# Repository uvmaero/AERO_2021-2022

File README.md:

# AERO_2021-2022

AERO Code and PCBs for CleanSpeed 5.0

This is all the boards and code we generate

## File Structure
Files here are for both the PCB and the firmware. 

{Board_Name}/{Board_Name_Firmware} -> holds the files for the firmware

{Board_Name}/{Board_Name_PCB} -> holds the KiCad files for the PCB

## Board Information

 - BCP: BMS Connector Pass through
 - DCB: Driver Contorl Board
 - HVB: High Voltage Board
 - MRP: Motor Resolver Passthrough
 - RCB: Rear Control Board

To read more about the boards go to [Board Descriptions](Board_Descriptions.md)

## Code Information

Code descrpitions can be found in [Firmware Descriptions](Firmware_Descriptions.md)

## Wireless Transceiver Information

There's also a wireless project. More information to come.

## Willem Review Notes: 

@Willem -> put any notes you have regarding boards here. 
Please review RCB, DCB, HVB, PAM

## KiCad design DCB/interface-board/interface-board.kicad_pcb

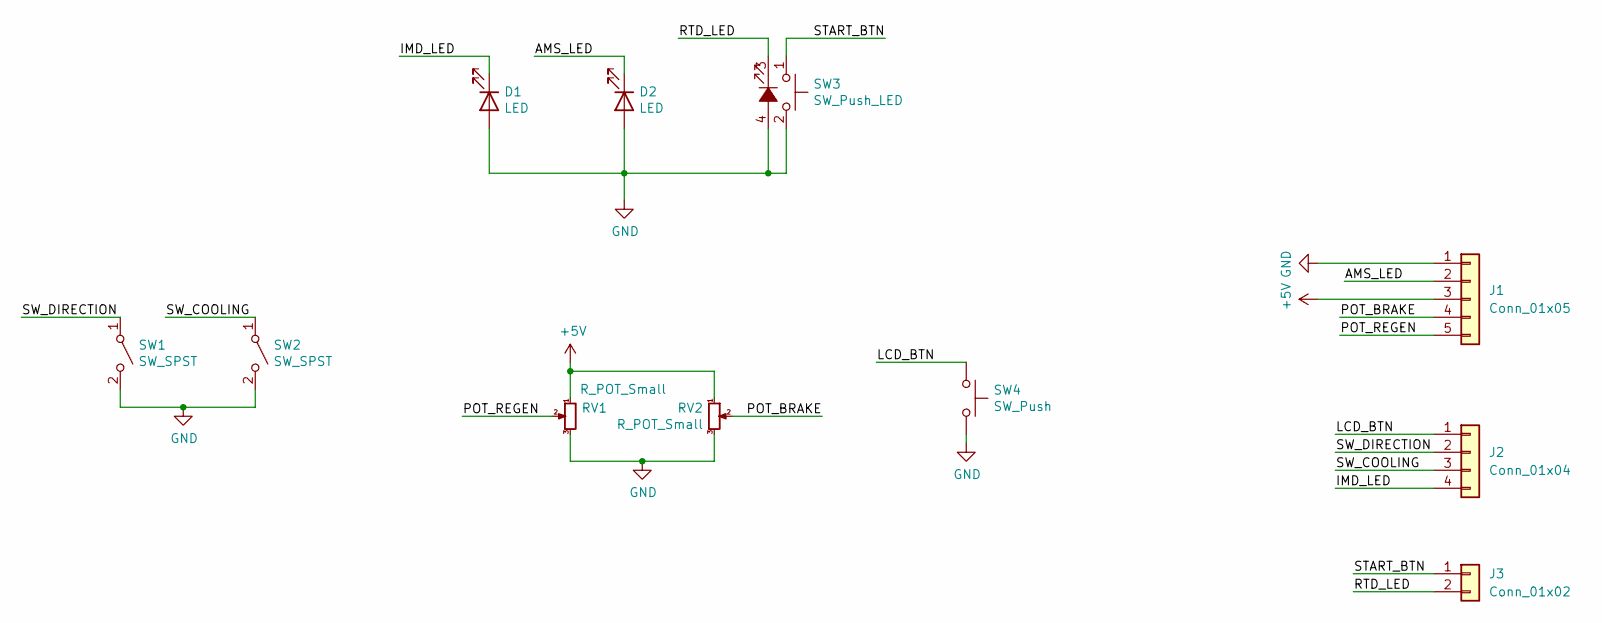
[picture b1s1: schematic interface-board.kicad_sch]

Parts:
D1, D2: LED; LED_0603_1608Metric_Pad1.05x0.95mm_HandSolder
J1: Conn_01x05; JST_XH_S5B-XH-A_1x05_P2.50mm_Horizontal
J2: Conn_01x04; JST_XH_S4B-XH-A_1x04_P2.50mm_Horizontal
J3: Conn_01x02; JST_XH_S2B-XH-A_1x02_P2.50mm_Horizontal
RV1, RV2: R_POT_Small; SMD_Pot
SW1, SW2: SW_SPST; Toggle_Switch_100SP1T1B4M2QE
SW3: SW_Push_LED; LED_PUSHBUTTON
SW4: SW_Push; SW_PUSH_6mm

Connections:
+5V: J1.3, RV1.1, RV2.1
/AMS_LED: D2.1 (K), J1.2
/IMD_LED: D1.1 (K), J2.4
/LCD_BTN: J2.1, SW4.1
/POT_BRAKE: J1.4, RV2.2
/POT_REGEN: J1.5, RV1.2
/RTD_LED: J3.2, SW3.3 (K)
/START_BTN: J3.1, SW3.1
/SW_COOLING: J2.3, SW2.1 (A)
/SW_DIRECTION: J2.2, SW1.1 (A)
GND: D1.2 (A), D2.2 (A), J1.1, RV1.3, RV2.3, SW1.2 (B), SW2.2 (B), SW3.2, SW3.4 (A), SW4.2

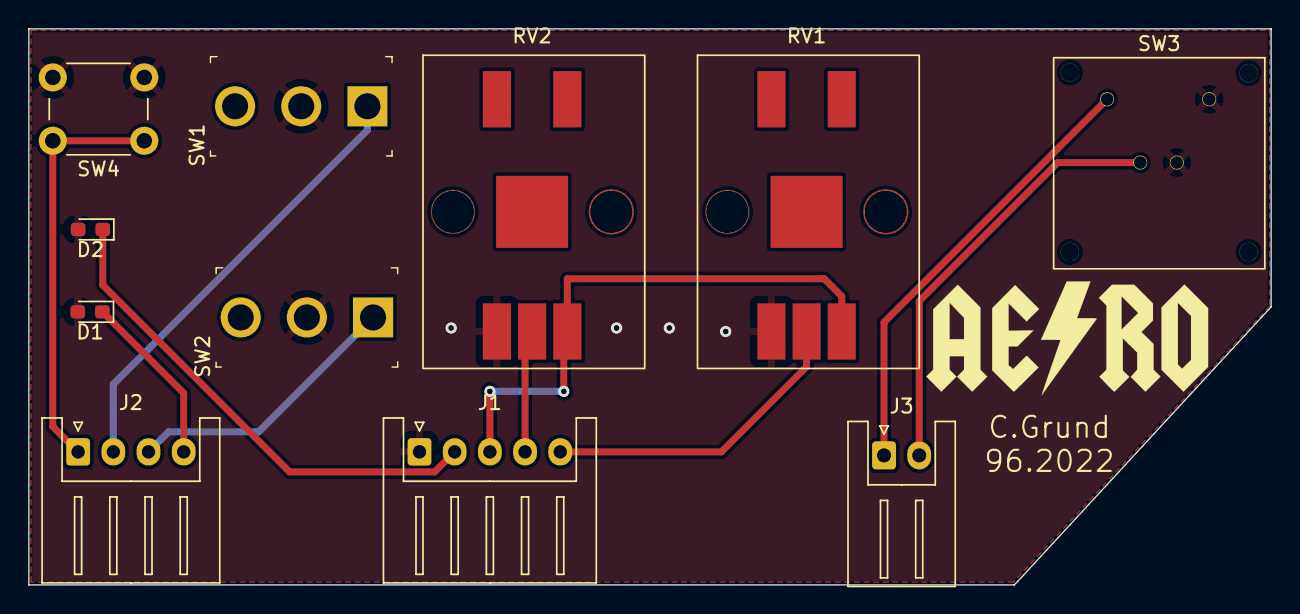
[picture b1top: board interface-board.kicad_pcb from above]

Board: 2 copper layers, 88.2 x 39.5 mm, 11 parts (0 on the bottom side), 11 nets.

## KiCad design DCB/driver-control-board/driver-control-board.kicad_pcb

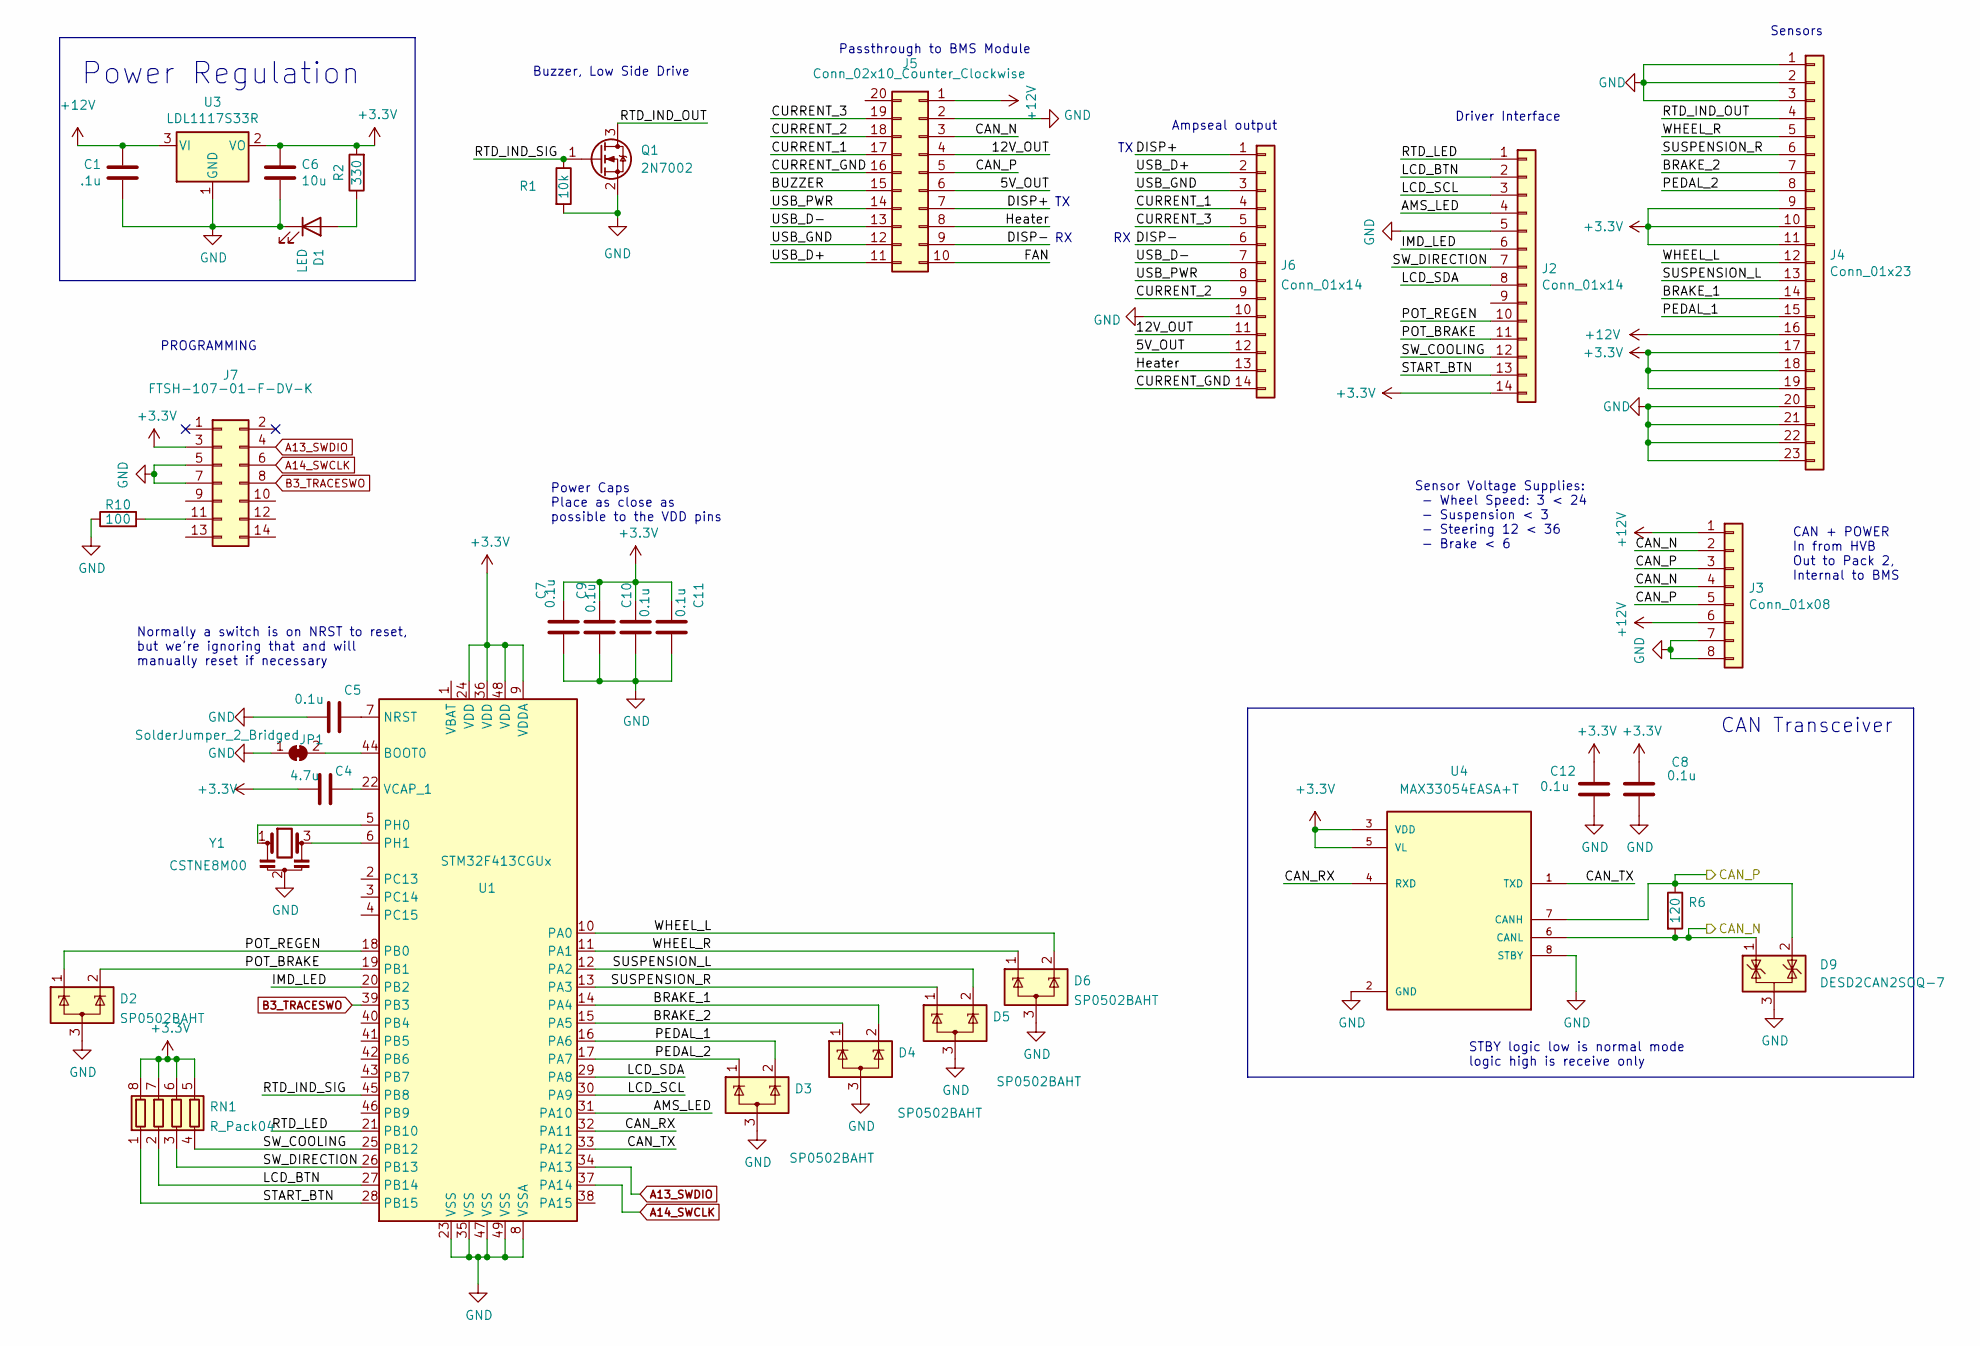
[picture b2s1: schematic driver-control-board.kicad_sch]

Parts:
C1: .1u; C_0603_1608Metric_Pad1.08x0.95mm_HandSolder
C4: 4.7u; C_0603_1608Metric_Pad1.08x0.95mm_HandSolder
C5, C7, C8, C9, C10, C11, C12: 0.1u; C_0603_1608Metric_Pad1.08x0.95mm_HandSolder
C6: 10u; C_0603_1608Metric_Pad1.08x0.95mm_HandSolder
D1: LED; LED_0603_1608Metric_Pad1.05x0.95mm_HandSolder
D2, D3, D4, D5, D6: SP0502BAHT; SOT-23
D9: DESD2CAN2SOQ-7; SOT-23
J2, J6: Conn_01x14; TE_1-776266-1_14pin_Horizontal
J3: Conn_01x08; TE_1-776280-1_8pin_Horizontal
J4: Conn_01x23; TE_1-770669-1_23pin_Horizontal
J5: Conn_02x10_Counter_Clockwise; PinHeader_2x10_P2.54mm_Horizontal
J7: FTSH-107-01-F-DV-K; PinHeader_2x07_P1.27mm_Vertical_SMD
JP1: SolderJumper_2_Bridged; SolderJumper-2_P1.3mm_Bridged_Pad1.0x1.5mm
Q1: 2N7002; SOT-23
R1: 10k; R_0603_1608Metric_Pad0.98x0.95mm_HandSolder
R2: 330; R_0603_1608Metric_Pad0.98x0.95mm_HandSolder
R6: 120; R_0603_1608Metric_Pad0.98x0.95mm_HandSolder
R10: 100; R_0603_1608Metric_Pad0.98x0.95mm_HandSolder
RN1: R_Pack04; R_Array_Convex_4x1206
U1: STM32F413CGUx; QFN-48-1EP_7x7mm_P0.5mm_EP5.6x5.6mm
U3: LDL1117S33R; SOT-223-3_TabPin2
U4: MAX33054EASA+T; SOIC127P600X175-8N
Y1: CSTNE8M00; Resonator_SMD_muRata_CSTxExxV-3Pin_3.0x1.1mm_HandSoldering

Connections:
+3V3: C4.2, C6.1, C7.1, C8.1, C9.1, C10.1, C11.1, C12.1, J2.14, J4.9, J4.10, J4.11, J4.17, J4.18, J4.19, J7.3, R2.2, RN1.5 (R4.2), RN1.6 (R3.2), RN1.7 (R2.2), RN1.8 (R1.2), U1.9 (VDDA), U1.24 (VDD), U1.36 (VDD), U1.48 (VDD), U3.2 (VO), U4.3 (VDD), U4.5 (VL)
+12V: C1.1, J3.1, J3.6, J4.16, J5.1, U3.3 (VI)
/5V_OUT: J5.6, J6.12
/12V_OUT: J5.4, J6.11
/AMS_LED: J2.4, U1.31 (PA10)
/BRAKE_1: D4.2 (K), J4.14, U1.14 (PA4)
/BRAKE_2: D4.1 (K), J4.7, U1.15 (PA5)
/BUZZER: J5.15
/CAN_N: D9.1 (K), J3.2, J3.4, J5.3, R6.2, U4.6 (CANL)
/CAN_P: D9.2 (K), J3.3, J3.5, J5.5, R6.1, U4.7 (CANH)
/CAN_RX: U1.32 (PA11), U4.4 (RXD)
/CAN_TX: U1.33 (PA12), U4.1 (TXD)
/CURRENT_1: J5.17, J6.4
/CURRENT_2: J5.18, J6.9
/CURRENT_3: J5.19, J6.5
/CURRENT_GND: J5.16, J6.14
/DISP+: J5.7, J6.1
/DISP-: J5.9, J6.6
/FAN: J5.10
/Heater: J5.8, J6.13
/IMD_LED: J2.6, U1.20 (PB2)
/LCD_BTN: J2.2, RN1.2 (R2.1), U1.27 (PB14)
/LCD_SCL: J2.3, U1.30 (PA9)
/LCD_SDA: J2.8, U1.29 (PA8)
/PEDAL_1: D3.2 (K), J4.15, U1.16 (PA6)
/PEDAL_2: D3.1 (K), J4.8, U1.17 (PA7)
/POT_BRAKE: D2.2 (K), J2.11, U1.19 (PB1)
/POT_REGEN: D2.1 (K), J2.10, U1.18 (PB0)
/RTD_IND_OUT: J4.4, Q1.3 (D)
/RTD_IND_SIG: Q1.1 (G), R1.1, U1.45 (PB8)
/RTD_LED: J2.1, U1.21 (PB10)
/START_BTN: J2.13, RN1.1 (R1.1), U1.28 (PB15)
/SUSPENSION_L: D5.2 (K), J4.13, U1.12 (PA2)
/SUSPENSION_R: D5.1 (K), J4.6, U1.13 (PA3)
/SW_COOLING: J2.12, RN1.4 (R4.1), U1.25 (PB12)
/SW_DIRECTION: J2.7, RN1.3 (R3.1), U1.26 (PB13)
/USB_D+: J5.11, J6.2
/USB_D-: J5.13, J6.7
/USB_GND: J5.12, J6.3
/USB_PWR: J5.14, J6.8
/WHEEL_L: D6.2 (K), J4.12, U1.10 (PA0)
/WHEEL_R: D6.1 (K), J4.5, U1.11 (PA1)
A13_SWDIO: J7.4, U1.34 (PA13)
A14_SWCLK: J7.6, U1.37 (PA14)
B3_TRACESWO: J7.8, U1.39 (PB3)
GND: C1.2, C5.2, C6.2, C7.2, C8.2, C9.2, C10.2, C11.2, C12.2, D1.1 (K), D2.3 (A), D3.3 (A), D4.3 (A), D5.3 (A), D6.3 (A), D9.3 (A), J2.5, J3.7, J3.8, J4.1, J4.2, J4.3, J4.20, J4.21, J4.22, J4.23, J5.2, J6.10, J7.5, J7.7, JP1.1 (A), Q1.2 (S), R1.2, R10.1, U1.8 (VSSA), U1.23 (VSS), U1.35 (VSS), U1.47 (VSS), U1.49 (VSS), U3.1 (GND), U4.2 (GND), U4.8 (STBY), Y1.2
unnamed: C4.1, U1.22 (VCAP_1)
unnamed: C5.1, U1.7 (NRST)
unnamed: D1.2 (A), R2.1
unnamed: J7.11, R10.2
unnamed: JP1.2 (B), U1.44 (BOOT0)
unnamed: U1.5 (PH0), Y1.1
unnamed: U1.6 (PH1), Y1.3

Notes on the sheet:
Ampseal output
Sensor Voltage Supplies: - Wheel Speed: 3 < 24 - Suspension < 3 - Steering 12 < 36 - Brake < 6
CAN + POWER In from HVB Out to Pack 2, Internal to BMS
CAN Transceiver
Normally a switch is on NRST to reset, but we're ignoring that and will manually reset if necessary
Buzzer, Low Side Drive
Driver Interface
Power Caps Place as close as possible to the VDD pins
Power Regulation
Sensors
STBY logic low is normal mode logic high is receive only
Passthrough to BMS Module
PROGRAMMING

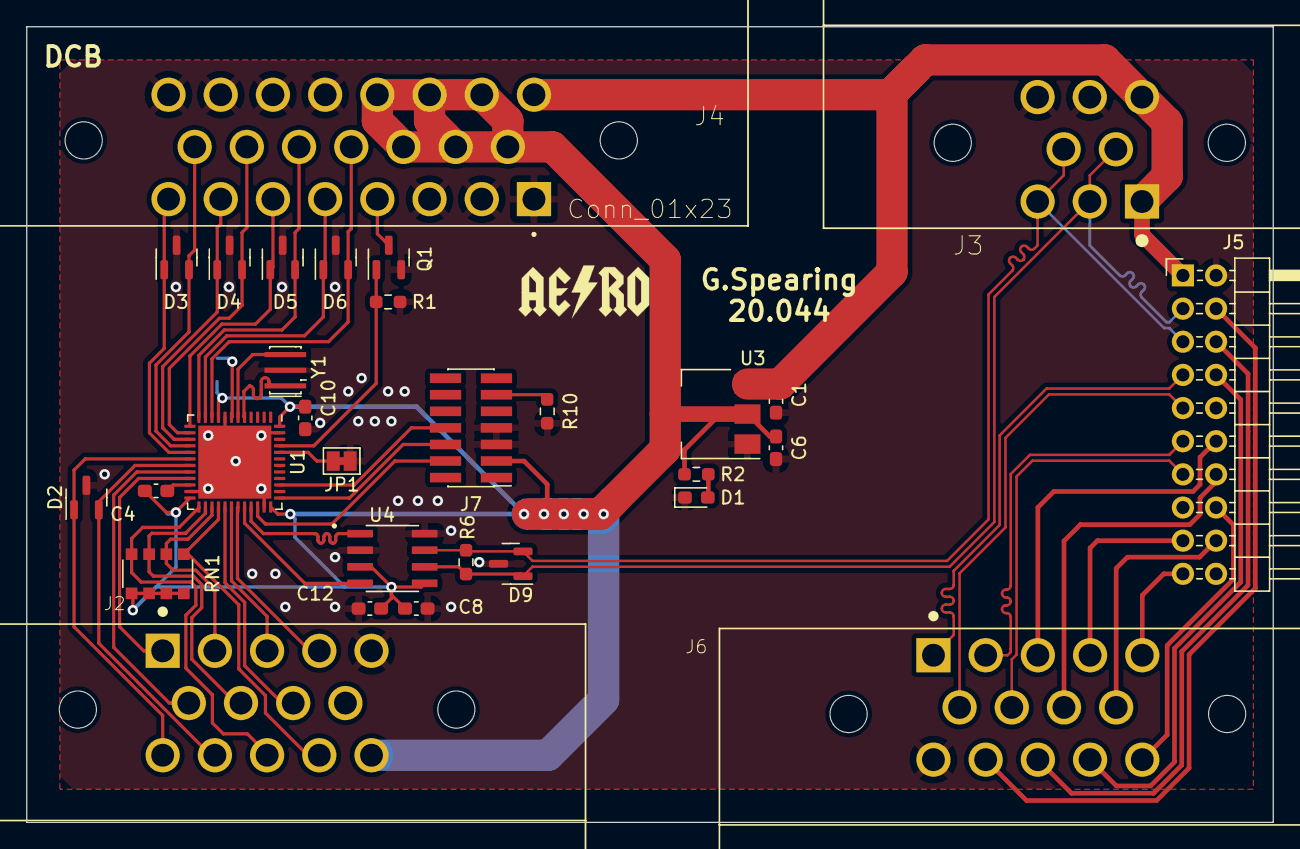
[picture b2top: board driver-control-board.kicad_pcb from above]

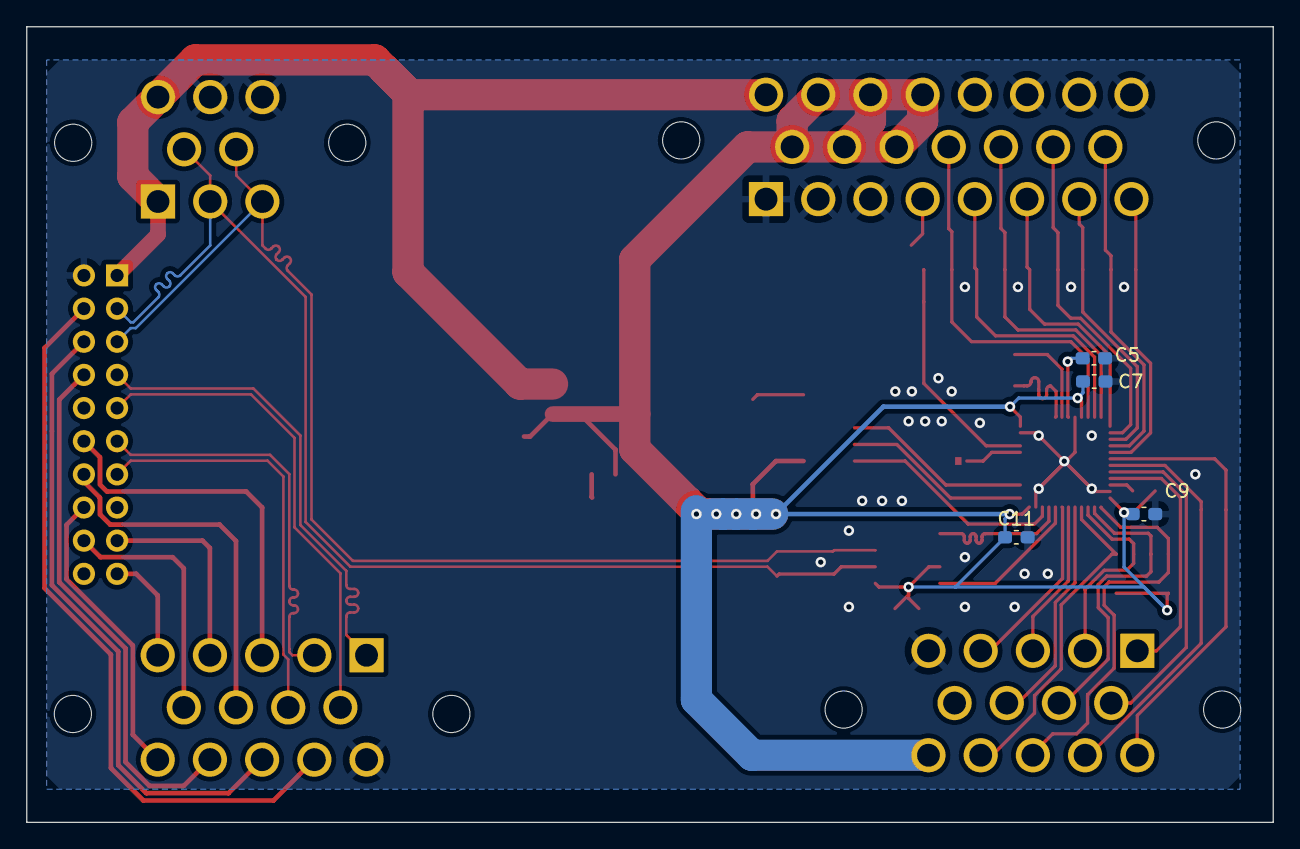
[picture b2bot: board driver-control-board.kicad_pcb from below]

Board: 2 copper layers, 95.5 x 61.0 mm, 34 parts (4 on the bottom side), 51 nets.

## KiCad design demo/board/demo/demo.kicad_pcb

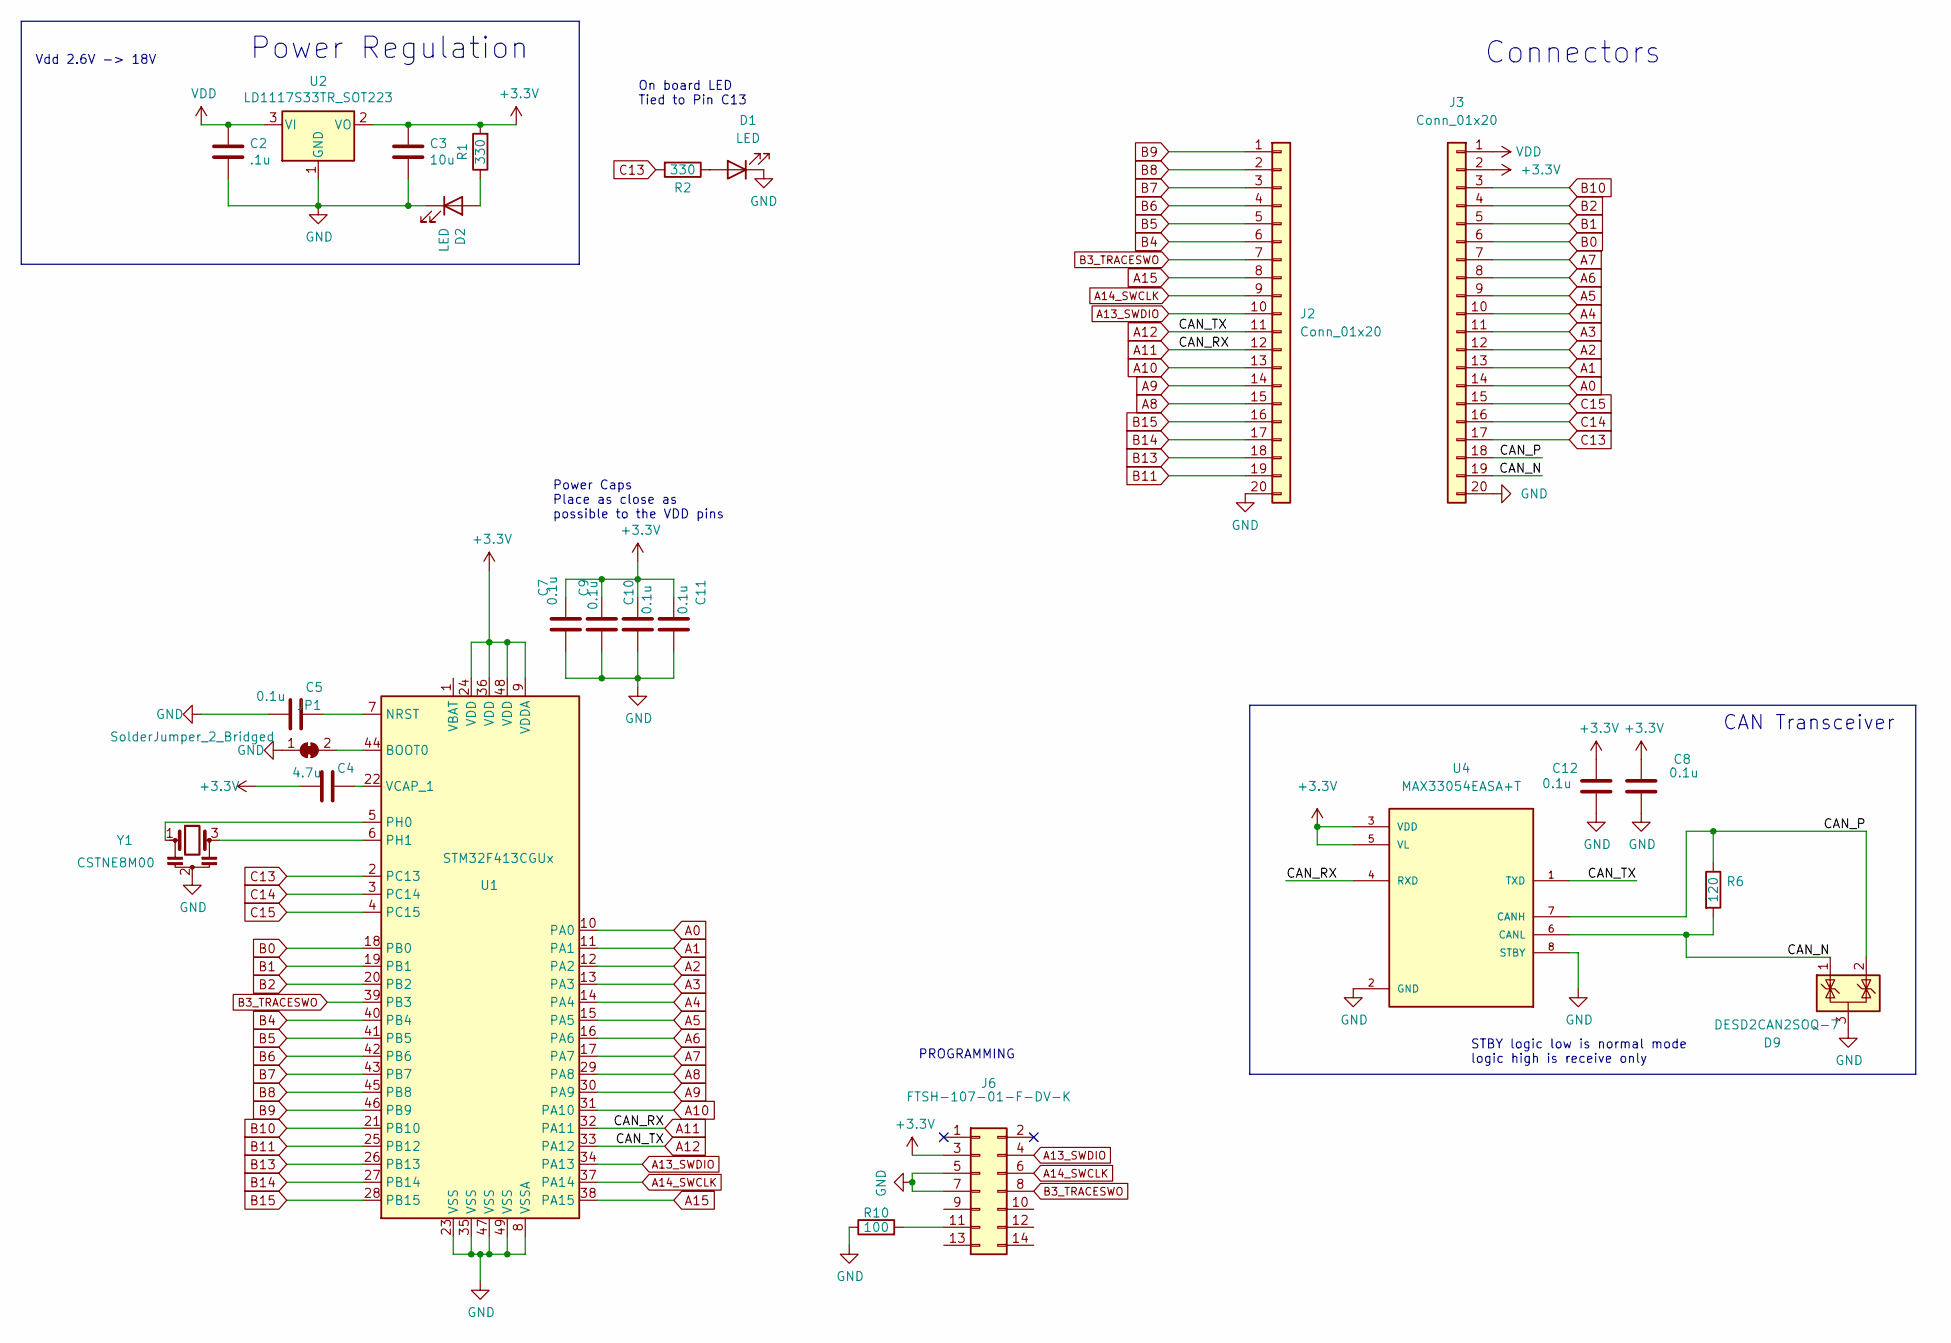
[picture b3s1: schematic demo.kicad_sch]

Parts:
C2: .1u; C_0603_1608Metric_Pad1.08x0.95mm_HandSolder
C3: 10u; C_0603_1608Metric_Pad1.08x0.95mm_HandSolder
C4: 4.7u; C_0603_1608Metric_Pad1.08x0.95mm_HandSolder
C5, C7, C8, C9, C10, C11, C12: 0.1u; C_0603_1608Metric_Pad1.08x0.95mm_HandSolder
D1, D2: LED; LED_0603_1608Metric_Pad1.05x0.95mm_HandSolder
D9: DESD2CAN2SOQ-7; SOT-23
J2, J3: Conn_01x20; PinHeader_1x20_P2.54mm_Vertical
J6: FTSH-107-01-F-DV-K; PinHeader_2x07_P1.27mm_Vertical_SMD
JP1: SolderJumper_2_Bridged; SolderJumper-2_P1.3mm_Bridged_RoundedPad1.0x1.5mm
R1, R2: 330; R_0603_1608Metric_Pad0.98x0.95mm_HandSolder
R6: 120; R_0603_1608Metric_Pad0.98x0.95mm_HandSolder
R10: 100; R_0603_1608Metric_Pad0.98x0.95mm_HandSolder
U1: STM32F413CGUx; QFN-48-1EP_7x7mm_P0.5mm_EP5.6x5.6mm
U2: LD1117S33TR_SOT223; SOT-223-3_TabPin2
U4: MAX33054EASA+T; SOIC127P600X175-8N
Y1: CSTNE8M00; Resonator_SMD_muRata_CSTxExxV-3Pin_3.0x1.1mm_HandSoldering

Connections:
+3V3: C3.1, C4.2, C7.1, C8.1, C9.1, C10.1, C11.1, C12.1, J3.2, J6.3, R1.2, U1.9 (VDDA), U1.24 (VDD), U1.36 (VDD), U1.48 (VDD), U2.2 (VO), U4.3 (VDD), U4.5 (VL)
/CAN_N: D9.1 (K), J3.19, R6.2, U4.6 (CANL)
/CAN_P: D9.2 (K), J3.18, R6.1, U4.7 (CANH)
A0: J3.14, U1.10 (PA0)
A1: J3.13, U1.11 (PA1)
A2: J3.12, U1.12 (PA2)
A3: J3.11, U1.13 (PA3)
A4: J3.10, U1.14 (PA4)
A5: J3.9, U1.15 (PA5)
A6: J3.8, U1.16 (PA6)
A7: J3.7, U1.17 (PA7)
A8: J2.15, U1.29 (PA8)
A9: J2.14, U1.30 (PA9)
A10: J2.13, U1.31 (PA10)
A11: J2.12, U1.32 (PA11), U4.4 (RXD)
A12: J2.11, U1.33 (PA12), U4.1 (TXD)
A13_SWDIO: J2.10, J6.4, U1.34 (PA13)
A14_SWCLK: J2.9, J6.6, U1.37 (PA14)
A15: J2.8, U1.38 (PA15)
B0: J3.6, U1.18 (PB0)
B1: J3.5, U1.19 (PB1)
B2: J3.4, U1.20 (PB2)
B3_TRACESWO: J2.7, J6.8, U1.39 (PB3)
B4: J2.6, U1.40 (PB4)
B5: J2.5, U1.41 (PB5)
B6: J2.4, U1.42 (PB6)
B7: J2.3, U1.43 (PB7)
B8: J2.2, U1.45 (PB8)
B9: J2.1, U1.46 (PB9)
B10: J3.3, U1.21 (PB10)
B11: J2.19, U1.25 (PB12)
B13: J2.18, U1.26 (PB13)
B14: J2.17, U1.27 (PB14)
B15: J2.16, U1.28 (PB15)
C13: J3.17, R2.2, U1.2 (PC13)
C14: J3.16, U1.3 (PC14)
C15: J3.15, U1.4 (PC15)
GND: C2.2, C3.2, C5.2, C7.2, C8.2, C9.2, C10.2, C11.2, C12.2, D1.1 (K), D2.1 (K), D9.3 (A), J2.20, J3.20, J6.5, J6.7, JP1.1 (A), R10.1, U1.8 (VSSA), U1.23 (VSS), U1.35 (VSS), U1.47 (VSS), U1.49 (VSS), U2.1 (GND), U4.2 (GND), U4.8 (STBY), Y1.2
unnamed: C4.1, U1.22 (VCAP_1)
unnamed: C5.1, U1.7 (NRST)
unnamed: D1.2 (A), R2.1
unnamed: D2.2 (A), R1.1
unnamed: J6.11, R10.2
unnamed: U1.5 (PH0), Y1.1
unnamed: U1.6 (PH1), Y1.3
unnamed: JP1.2 (B), U1.44 (BOOT0)
VDD: C2.1, J3.1, U2.3 (VI)

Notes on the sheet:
CAN Transceiver
On board LED Tied to Pin C13
Vdd 2.6V -> 18V
Power Regulation
Connectors
Power Caps Place as close as possible to the VDD pins
STBY logic low is normal mode logic high is receive only
PROGRAMMING

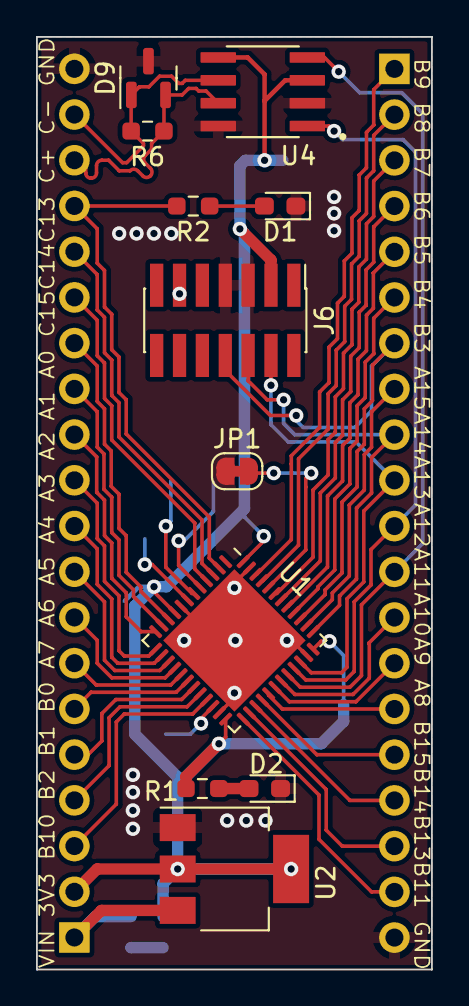
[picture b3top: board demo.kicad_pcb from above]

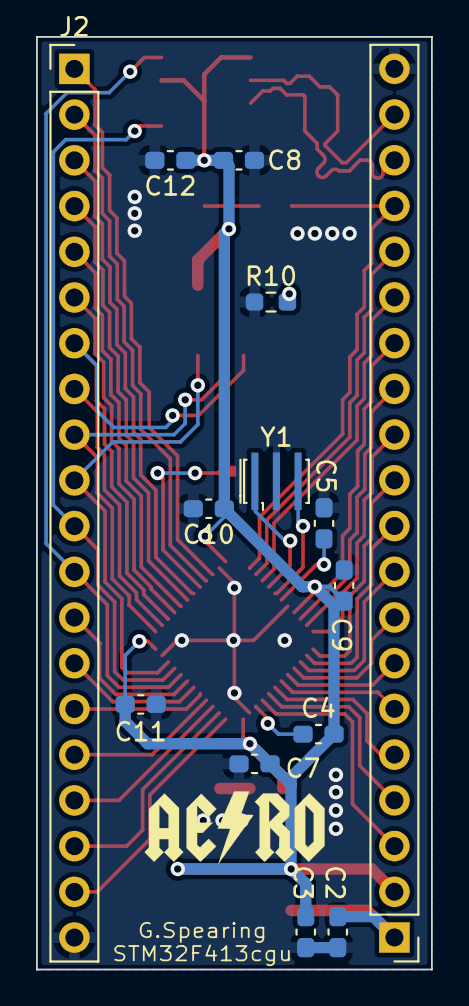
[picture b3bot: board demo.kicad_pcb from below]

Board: 2 copper layers, 21.9 x 51.8 mm, 25 parts (14 on the bottom side), 47 nets.

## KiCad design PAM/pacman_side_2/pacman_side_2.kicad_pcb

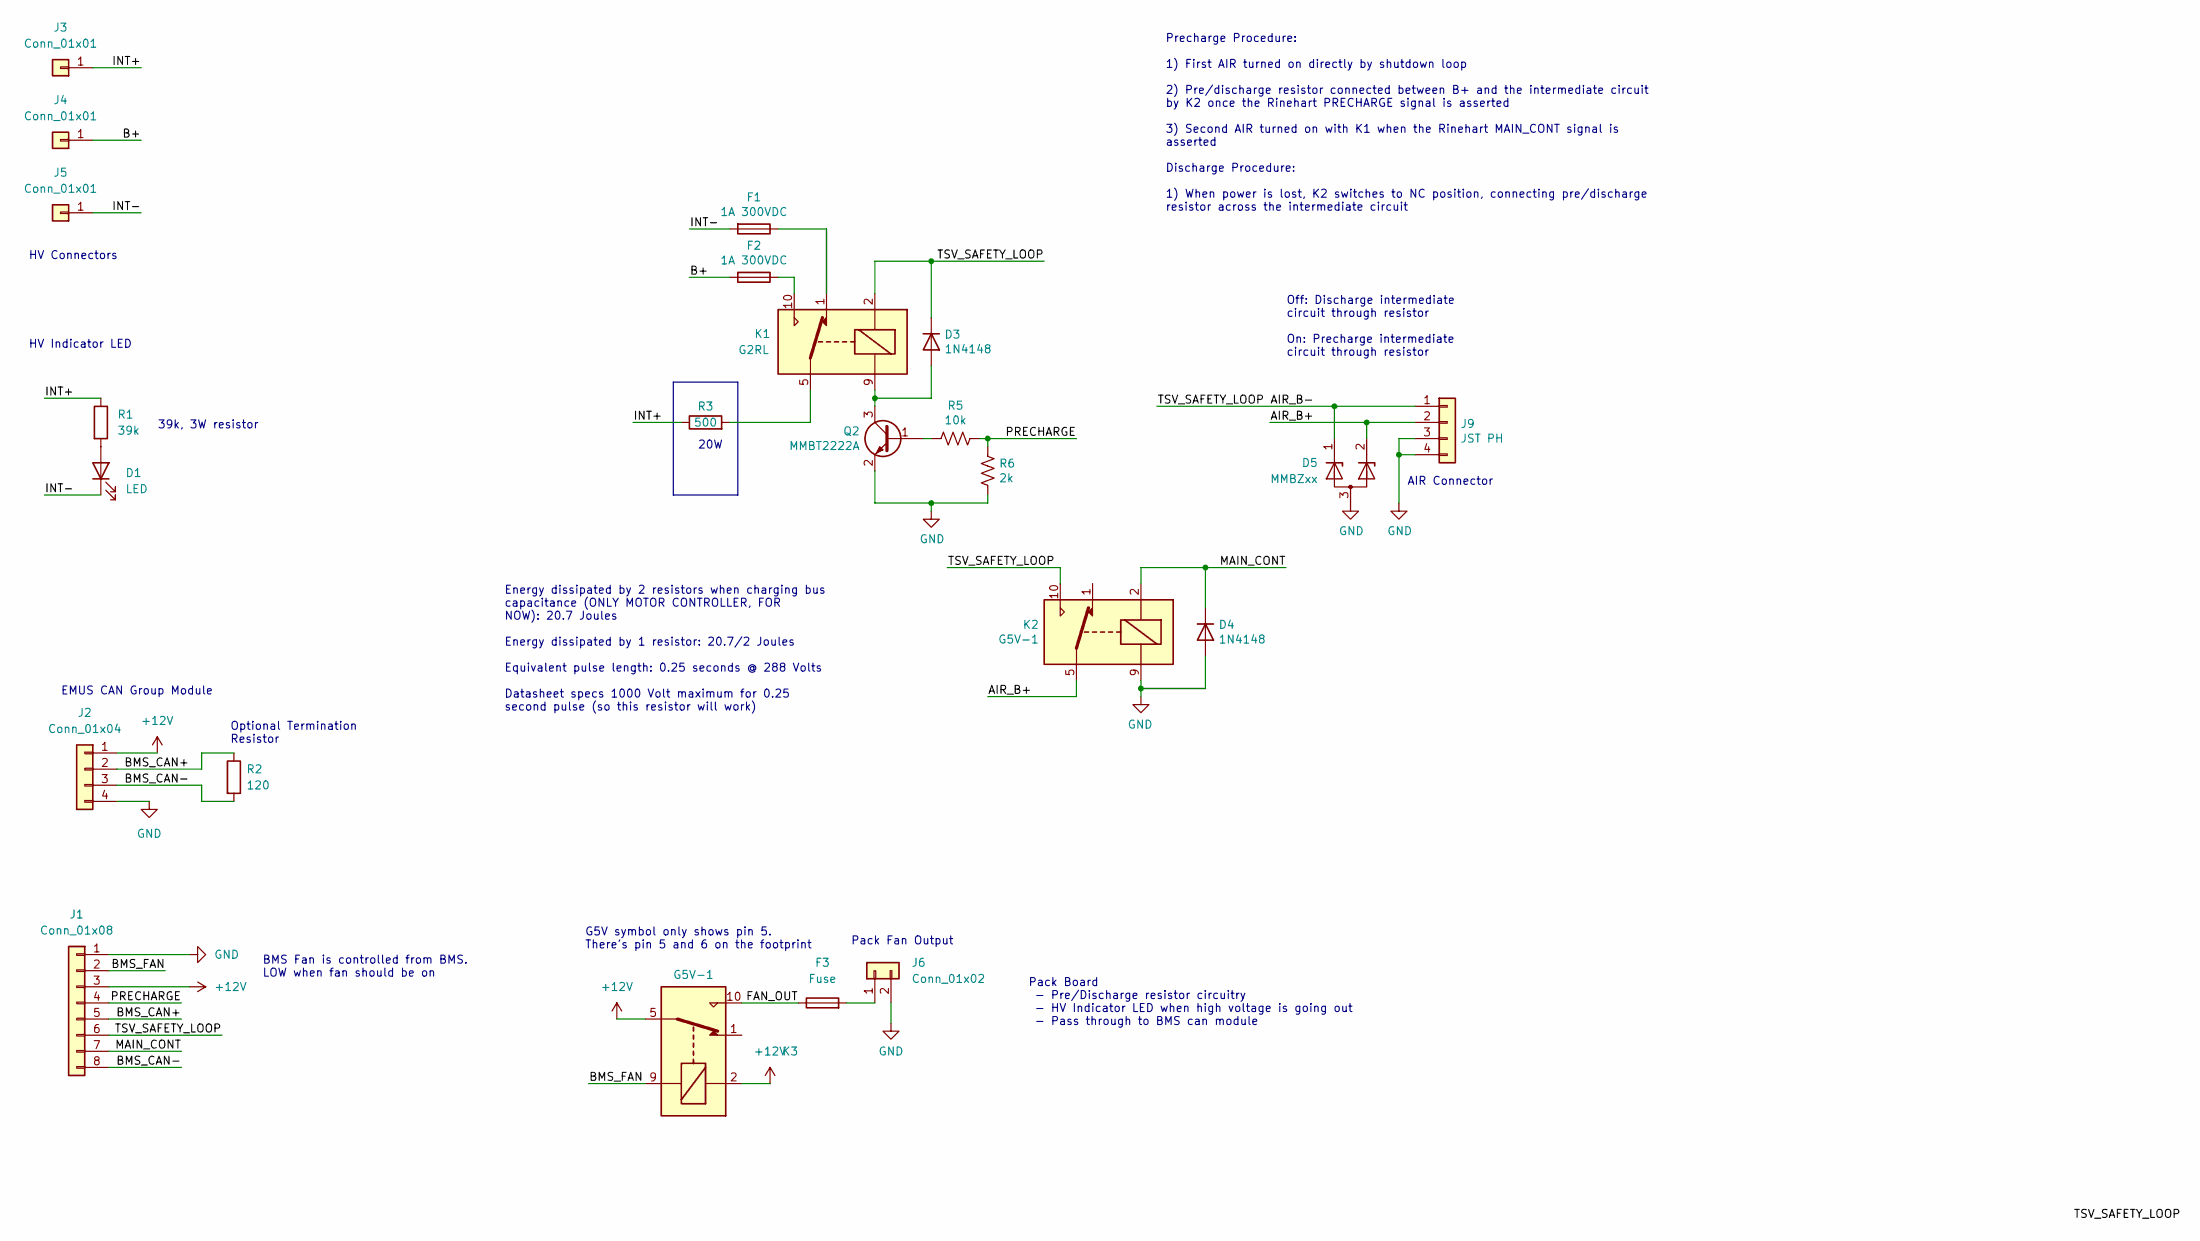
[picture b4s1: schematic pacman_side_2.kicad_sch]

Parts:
D1: LED; LPA-C011301S-x LED 0805 LIGHT PIPE SINGLE VERT SMD
D3, D4: 1N4148; D_MiniMELF
D5: MMBZxx; SOT-23
F1, F2: 1A 300VDC; Fuseholder_Cylinder-5x20mm_Schurter_0031_8201_Horizontal_Op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
F3: Fuse; Fuseholder_Blade_Mini_Keystone_3568
J1: Conn_01x08; TE_1-776276-1_8pin_Vertical
J2: Conn_01x04; JST_XH_B4B-XH-A_1x04_P2.50mm_Vertical
J3, J4, J5: Conn_01x01; Hirose_DF63M-1P-3.96DSA_1x01_P3.96mm_Vertical
J6: Conn_01x02; JST_XH_B2B-XH-A_1x02_P2.50mm_Vertical
J9: JST PH; JST_PH_B4B-PH-K_1x04_P2.00mm_Vertical
K1: G2RL
K2, K3: G5V-1; Relay_SPDT_Omron_G5V-1
Q2: MMBT2222A; SOT-23
R1: 39k; R_Axial_DIN0414_L11.9mm_D4.5mm_P25.40mm_Horizontal
R2: 120; R_0603_1608Metric_Pad0.98x0.95mm_HandSolder
R3: 500; TO-220-2_Horizontal_TabDown
R5: 10k; R_0603_1608Metric
R6: 2k; R_0603_1608Metric

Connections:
+12V: J1.3, J2.1, K3.2, K3.5, K3.6
/AIR_B+: D5.2 (K), J9.2, K2.5, K2.6
/AIR_B-: D3.1 (K), D5.1 (K), J1.6, J9.1, K1.2, K2.10
/B+: F2.2, J4.1
/BMS_CAN+: J1.5, J2.2, R2.1
/BMS_CAN-: J1.8, J2.3, R2.2
/BMS_FAN: J1.2, K3.9
/FAN_OUT: F3.1, K3.10
/INT+: J3.1, R1.1, R3.1
/INT-: D1.1 (K), F1.2, J5.1
/MAIN_CONT: D4.1 (K), J1.7, K2.2
/PRECHARGE: J1.4, R5.2, R6.2
GND: D4.2 (A), D5.3 (A), J1.1, J2.4, J6.2, J9.3, J9.4, K2.9, Q2.2 (E), R6.1
unnamed: D1.2 (A), R1.2
unnamed: D3.2 (A), K1.9, Q2.3 (C)
unnamed: F1.1, K1.1
unnamed: F2.1, K1.10
unnamed: F3.2, J6.1
unnamed: K1.5, K1.6, R3.2
unnamed: Q2.1 (B), R5.1

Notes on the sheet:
EMUS CAN Group Module
Precharge Procedure: 1) First AIR turned on directly by shutdown loop 2) Pre/discharge resistor connected between B+ and the intermediate circuit by K2 once the Rinehart PRECHARGE signal is asserted 3) Second AIR turned on with K1 when the Rinehart MAIN_CONT signal is asserted Discharge Procedure: 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
AIR Connector
20W
39k, 3W resistor
Pack Fan Output
Energy dissipated by 2 resistors when charging bus capacitance (ONLY MOTOR CONTROLLER, FOR NOW): 20.7 Joules Energy dissipated by 1 resistor: 20.7/2 Joules Equivalent pulse length: 0.25 seconds @ 288 Volts Datasheet specs 1000 Volt maximum for 0.25 second pulse (so this resistor will work)
Optional Termination Resistor
Off: Discharge intermediate circuit through resistor On: Precharge intermediate circuit through resistor
G5V symbol only shows pin 5. There's pin 5 and 6 on the footprint
HV Connectors
BMS Fan is controlled from BMS. LOW when fan should be on
Pack Board - Pre/Discharge resistor circuitry - HV Indicator LED when high voltage is going out - Pass through to BMS can module
HV Indicator LED

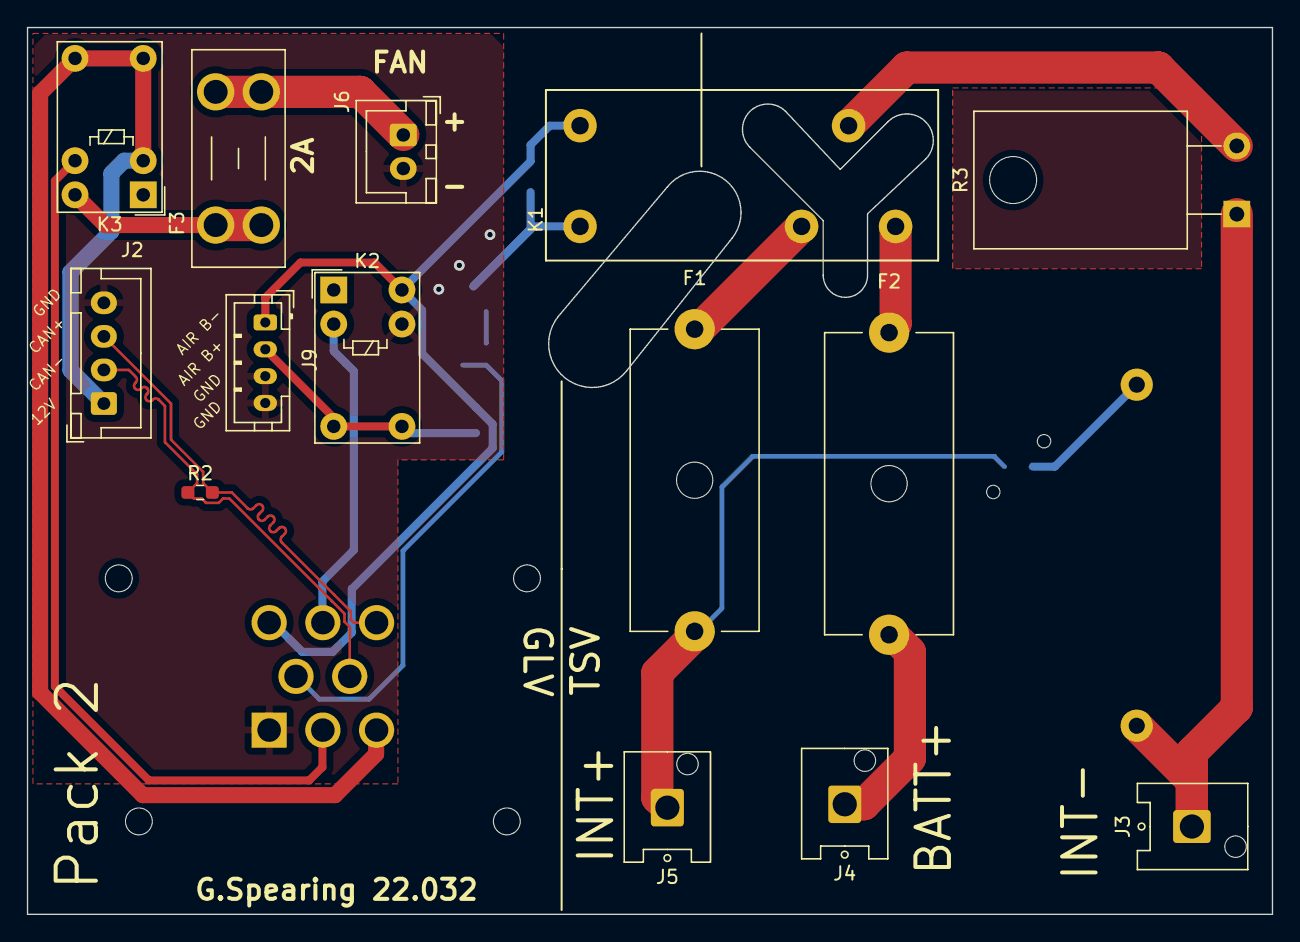
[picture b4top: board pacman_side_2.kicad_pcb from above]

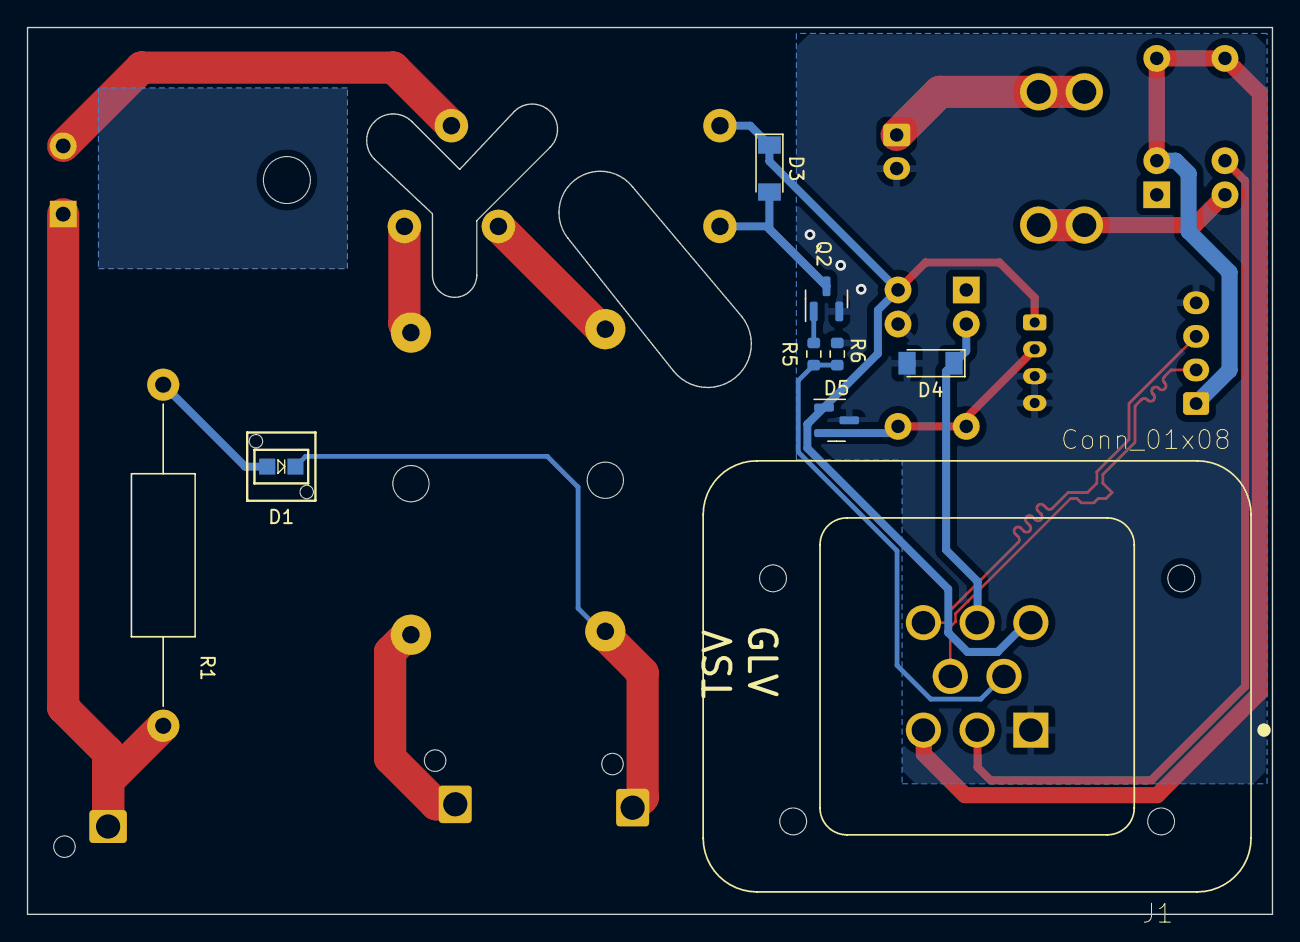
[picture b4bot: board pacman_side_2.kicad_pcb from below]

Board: 2 copper layers, 92.7 x 66.0 mm, 23 parts (9 on the bottom side), 20 nets.
